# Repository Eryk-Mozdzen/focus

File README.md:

# FOCUS - BLDC motor control library

## Features

- FOC current loop implementation
- AB, AB+index, absolute encoder support
- [Sliding Mode Observer](https://www.mathworks.com/help/mcb/ref/slidingmodeobserver.html) method support
- [High Frequency Injection](https://www.sciencedirect.com/science/article/pii/S2214914723002155?fr=RR-2&ref=pdf_download&rr=a5664e15cb732783) method support
- automatic motor tunning
- C source code without external dependencies (even for `libm`)

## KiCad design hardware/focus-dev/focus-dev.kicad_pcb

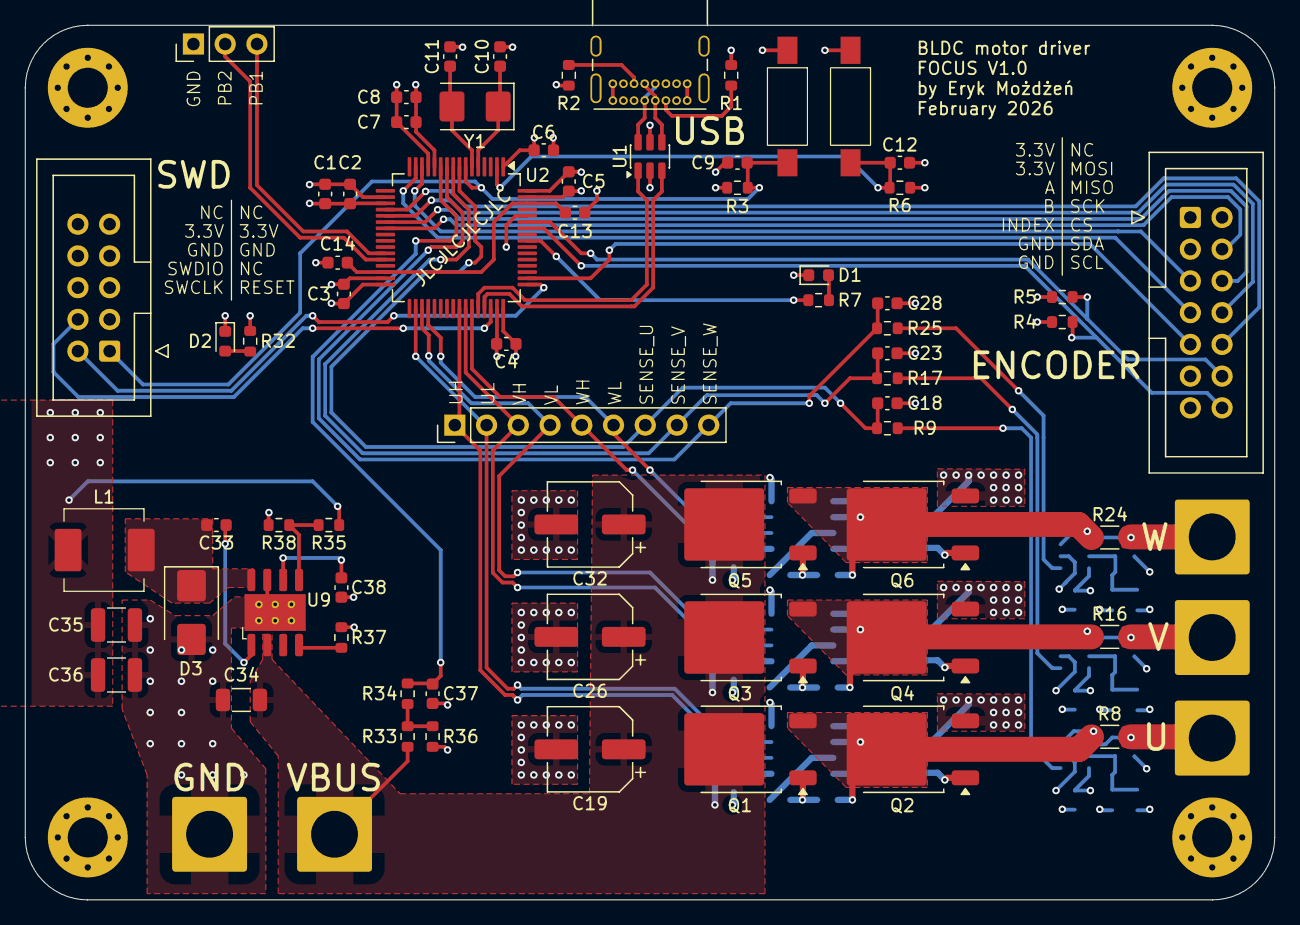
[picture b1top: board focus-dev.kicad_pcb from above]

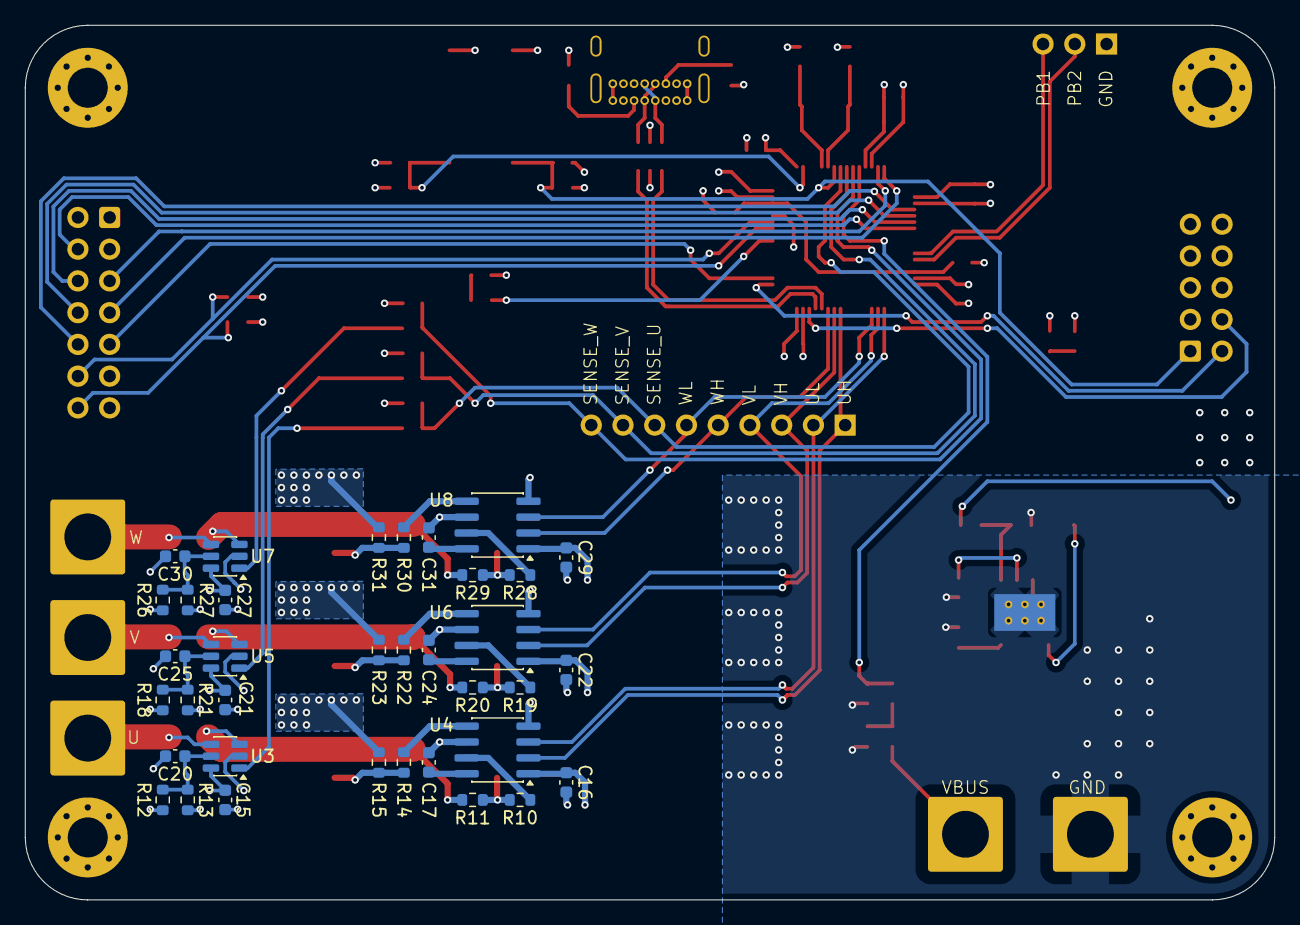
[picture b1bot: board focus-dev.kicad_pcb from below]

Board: 4 copper layers, 100.0 x 70.0 mm, 112 parts (36 on the bottom side), 73 nets.

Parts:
C1: 4.7u; C_0603_1608Metric
C2, C3, C4, C5, C6, C7, C9, C12, C15, C18, C20, C21, C23, C25, C27, C28, C30, C37: 100n; C_0603_1608Metric
C8: 1u; C_0603_1608Metric
C10, C11: 22p; C_0603_1608Metric
C13, C14: 2.2u; C_0603_1608Metric
C16, C22, C29: 1u/50V; C_0603_1608Metric
C17, C24, C31, C33: 100n/50V; C_0603_1608Metric
C19, C26, C32: 47u/50V; CP_Elec_6.3x7.7
C34: 10u/50V; C_1206_3216Metric
C35, C36: 47u/16V; C_1210_3225Metric
C38: 22n; C_0603_1608Metric
D1: BLUE; D_0603_1608Metric
D2: RED; D_0603_1608Metric
D3: SK56; D_SMB
H1, H2, H3, H4: MountingHole_Pad; MountingHole_3.2mm_M3_Pad_Via
J1: IDC-10; IDC-Header_2x05_P2.54mm_Vertical
J2: USB_C_Receptacle_USB2.0_14P; USB_C_Receptacle_GCT_USB4085
J3: IDC-14; IDC-Header_2x07_P2.54mm_Vertical
J4: Conn_01x09; PinHeader_1x09_P2.54mm_Vertical
J5: Conn_01x03; PinHeader_1x03_P2.54mm_Vertical
J6, J7, J8, J9, J10: Conn_01x01; SolderWire-4sqmm_1x01_D3mm_OD6mm
L1: 6.8u/4.5A; PA4341.XXXNLT
Q1, Q2, Q3, Q4, Q5, Q6: IPD90N04S4L04; TO-252-2
R1, R2: 5.1k; R_0603_1608Metric
R3, R4, R5, R12, R13, R18, R21, R26, R27: 4.7k; R_0603_1608Metric
R6: 10k; R_0603_1608Metric
R7, R32: 1k; R_0603_1608Metric
R8, R16, R24: 2m; R_1206_3216Metric
R9, R17, R25, R34: 10; R_0603_1608Metric
R10, R14, R19, R22, R28, R30: 68; R_0603_1608Metric
R11, R15, R20, R23, R29, R31, R36: 47k; R_0603_1608Metric
R33: 470k; R_0603_1608Metric
R35: 100k/1%; R_0603_1608Metric
R37: 49.9k; R_0603_1608Metric
R38: 29.4k/1%; R_0603_1608Metric
SW1, SW2: SW_Push; spst_6x3mm
U1: USBLC6-2SC6; SOT-23-6
U2: STM32H523RET6; LQFP-64_10x10mm_P0.5mm
U3, U5, U7: INA181A3; SOT-23-6
U4, U6, U8: LM2105D; SOIC-8_3.9x4.9mm_P1.27mm
U9: LV14340
Y1: 8MHz; Crystal_SMD_5032-2Pin_5.0x3.2mm

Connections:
+3.3V: C1.1, C2.1, C3.1, C4.1, C5.1, C6.1, C7.1, C8.1, C15.1, C21.1, C27.1, C35.1, C36.1, J1.7, J1.8, J3.1, J3.3, L1.2, R3.1, R4.1, R5.1, R6.1, R12.2, R18.2, R26.2, R32.1, R35.1, U1.5 (VBUS), U2.1 (VBAT), U2.13 (VDDA), U2.19 (VDD), U2.32 (VDD), U2.48 (VDD), U2.64 (VDD), U3.6 (V+), U5.6 (V+), U7.6 (V+)
/control/ENCODER_A: J3.5, U2.14 (PA0)
/control/ENCODER_B: J3.7, U2.15 (PA1)
/control/ENCODER_I2C_SCL: J3.14, R4.2, U2.58 (PB6)
/control/ENCODER_I2C_SDA: J3.12, R5.2, U2.59 (PB7)
/control/ENCODER_INDEX: J3.9, U2.50 (PA15(JTDI))
/control/ENCODER_SPI_CS: J3.10, U2.20 (PA4)
/control/ENCODER_SPI_MISO: J3.6, U2.22 (PA6)
/control/ENCODER_SPI_MOSI: J3.4, U2.23 (PA7)
/control/ENCODER_SPI_SCK: J3.8, U2.21 (PA5)
/control/STM_OSC_IN: C10.1, U2.5 (PH0), Y1.1
/control/STM_OSC_OUT: C11.1, U2.6 (PH1), Y1.2
/control/STM_RESET: C9.1, J1.1, R3.2, SW1.2, U2.7 (NRST)
/control/STM_SWCLK: J1.2, U2.49 (PA14(JTCK)
/control/STM_SWDIO: J1.4, U2.46 (PA13(JTMS)
/control/STM_USB_D+: U1.3 (I/O2), U2.45 (PA12)
/control/STM_USB_D-: U1.1 (I/O1), U2.44 (PA11)
/control/STM_USER_BUTTON: C12.1, R6.2, SW2.2, U2.2 (PC13)
/control/STM_USER_GPIO1: J5.3, U2.27 (PB1)
/control/STM_USER_GPIO2: J5.2, U2.28 (PB2)
/control/STM_USER_LED: R7.1, U2.56 (PB4(NJTRST))
/control/STM_VCAP: C13.1, C14.1, U2.30 (VCAP), U2.62 (VCAP)
/control/USB_CC1: J2.A5 (CC1), R1.2
/control/USB_CC2: J2.B5 (CC2), R2.2
/control/USB_D+: J2.A6 (D+), J2.B6 (D+), U1.4 (I/O2)
/control/USB_D-: J2.A7 (D-), J2.B7 (D-), U1.6 (I/O1)
/inverter/PHASE_U: C17.2, Q1.3 (S), Q2.2 (D), R8.1, R11.2, U3.3 (+), U4.6 (SH)
/inverter/PHASE_V: C24.2, Q3.3 (S), Q4.2 (D), R16.1, R20.2, U5.3 (+), U6.6 (SH)
/inverter/PHASE_W: C31.2, Q5.3 (S), Q6.2 (D), R24.1, R29.2, U7.3 (+), U8.6 (SH)
GND: C1.2, C2.2, C3.2, C4.2, C5.2, C6.2, C7.2, C8.2, C9.2, C10.2, C11.2, C12.2, C13.2, C14.2, C15.2, C16.1, C18.2, C19.2, C20.2, C21.2, C22.1, C23.2, C25.2, C26.2, C27.2, C28.2, C29.1, C30.2, C32.2, C34.2, C35.2, C36.2, C37.2, C38.1, D1.1 (K), D2.1 (K), D3.2 (A), J1.5, J1.6, J2.A1 (GND), J2.A12 (GND), J2.B1 (GND), J2.B12 (GND), J3.11, J3.13, J5.1, J10.1, Q2.3 (S), Q4.3 (S), Q6.3 (S), R1.1, R2.1, R13.2, R15.2, R21.2, R23.2, R27.2, R31.2, R36.2, R37.2, R38.2, SW1.1, SW2.1, U1.2 (GND), U2.12 (VSSA), U2.18 (VSS), U2.31 (VSS), U2.47 (VSS), U2.60 (BOOT0), U2.63 (VSS), U3.2 (GND), U4.4 (GND), U5.2 (GND), U6.4 (GND), U7.2 (GND), U8.4 (GND), U9.7 (GND), U9.9 (PAD)
MOTOR_PWM_UH: J4.1, U2.41 (PA8), U4.2 (INH)
MOTOR_PWM_UL: J4.2, U2.34 (PB13), U4.3 (INL)
MOTOR_PWM_VH: J4.3, U2.42 (PA9), U6.2 (INH)
MOTOR_PWM_VL: J4.4, U2.35 (PB14), U6.3 (INL)
MOTOR_PWM_WH: J4.5, U2.43 (PA10), U8.2 (INH)
MOTOR_PWM_WL: J4.6, U2.36 (PB15), U8.3 (INL)
MOTOR_SENSE_U: C18.1, J4.7, R9.2, U2.8 (PC0)
MOTOR_SENSE_V: C23.1, J4.8, R17.2, U2.9 (PC1)
MOTOR_SENSE_W: C28.1, J4.9, R25.2, U2.10 (PC2)
unnamed: D1.2 (A), R7.2
unnamed: D2.2 (A), R32.2
unnamed: C33.2, D3.1 (K), L1.1, U9.8 (SW)
unnamed: J6.1, R8.2, U3.4 (-)
unnamed: J7.1, R16.2, U5.4 (-)
unnamed: J8.1, R24.2, U7.4 (-)
unnamed: Q1.1 (G), R10.2, R11.1
unnamed: Q2.1 (G), R14.2, R15.1
unnamed: Q3.1 (G), R19.2, R20.1
unnamed: Q4.1 (G), R22.2, R23.1
unnamed: Q5.1 (G), R28.2, R29.1
unnamed: Q6.1 (G), R30.2, R31.1
unnamed: R9.1, U3.1
unnamed: R17.1, U5.1
unnamed: R25.1, U7.1
unnamed: R33.2, R34.1, R36.1
unnamed: C20.1, R12.1, R13.1, U3.5 (REF)
unnamed: C17.1, U4.8 (BST)
unnamed: R10.1, U4.7 (GH)
unnamed: R14.1, U4.5 (GL)
unnamed: C25.1, R18.1, R21.1, U5.5 (REF)
unnamed: C24.1, U6.8 (BST)
unnamed: R19.1, U6.7 (GH)
unnamed: R22.1, U6.5 (GL)
unnamed: C30.1, R26.1, R27.1, U7.5 (REF)
unnamed: C31.1, U8.8 (BST)
unnamed: R28.1, U8.7 (GH)
unnamed: R30.1, U8.5 (GL)
unnamed: C33.1, U9.1 (BOOT)
unnamed: R35.2, R38.1, U9.5 (FB)
unnamed: R37.1, U9.4 (RT/SYNC)
unnamed: C38.2, U9.6 (SS)
POWER_SENSE: C37.1, R34.2, U2.11 (PC3)
VBUS: C16.2, C19.1, C22.2, C26.1, C29.2, C32.1, C34.1, J9.1, Q1.2 (D), Q3.2 (D), Q5.2 (D), R33.1, U4.1 (GVDD), U6.1 (GVDD), U8.1 (GVDD), U9.2 (VIN)

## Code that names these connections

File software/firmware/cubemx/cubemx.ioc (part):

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Mcu.Name=STM32H523RETx
Mcu.Package=LQFP64
Mcu.UserName=STM32H523RETx
PA0.Signal=S_TIM2_CH1
PA1.Signal=S_TIM2_CH2
PA10.Signal=S_TIM1_CH3
PA11.Mode=Device
PA11.Signal=USB_DM
PA12.Mode=Device
PA12.Signal=USB_DP
PA15(JTDI).Signal=S_TIM2_ETR
PA8.Signal=S_TIM1_CH1
PA9.Signal=S_TIM1_CH2
PB1.Signal=GPIO_Output
PB13.Mode=PWM Generation1 CH1 CH1N
PB13.Signal=TIM1_CH1N
PB14.Mode=PWM Generation2 CH2 CH2N
PB14.Signal=TIM1_CH2N
PB15.Mode=PWM Generation3 CH3 CH3N
PB15.Signal=TIM1_CH3N
PB2.Signal=GPIO_Output
PB4(NJTRST).Signal=GPIO_Output
PC0.Signal=ADCx_INP10
PC1.Signal=ADCx_INP11
PC13.Signal=GPIO_Input
PC2.Signal=ADCx_INP12
PC3.Signal=ADCx_INP13
PH0-OSC_IN(PH0).Mode=HSE-External-Oscillator
PH0-OSC_IN(PH0).Signal=RCC_OSC_IN
PH1-OSC_OUT(PH1).Mode=HSE-External-Oscillator
PH1-OSC_OUT(PH1).Signal=RCC_OSC_OUT
RCC.HSE_VALUE=8000000
RCC.SYSCLKFreq_VALUE=250000000
RCC.SYSCLKSource=RCC_SYSCLKSOURCE_PLLCLK
board=custom

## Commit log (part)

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2025-07-21 driver architecture
2025-07-22 basic foc
2025-07-22 memory
2025-07-24 move code to external directory
2026-01-01 trash
2026-01-04 wip: dev-board schematic
2026-01-28 wip: remove onboard encoders
2026-01-31 wip: layout
2026-02-01 wip: rest of the layout
2026-02-01 wip: change resistor value
2026-02-21 blink project
2026-02-21 TinyUSB CDC & MSC
2026-02-22 lwip, USB-Ethernet HTTP server
2026-02-22 remove FreeRTOS, add UDP stream
2026-02-23 wip: cleaning
2026-02-24 focus source code architecture
2026-02-26 MQTT pub/sub
2026-02-27 MSGPACK
2026-02-27 cleaning
2026-02-28 cleaning, PWM wip
2026-02-28 fix encoder index interrupt
2026-03-01 first motor spin
2026-03-02 first FOC
2026-03-04 wip: encoder misaligment calibration, proper SVPWM
2026-03-05 PWM 10kHz, preload disabled
2026-03-06 encoder eccentricity calibration, current offset calibration
2026-03-07 cleaner encoder calibration (still not work)
2026-03-08 poorly tuned FOC
2026-04-30 allow for uv
2026-04-30 telnet support
2026-05-03 FSM, move math to separate file
2026-05-03 automatic Rs Ld Lq estimation
2026-05-03 cleaning configs
2026-05-06 simplify PID antiwindup logic
2026-05-07 fix dt pid
2026-05-07 calibration of current offset and scale
2026-05-08 wip: FOC works, example PD for position control
2026-05-09 reorganize repo files
2026-05-09 fix build system
2026-05-10 remove open loop
2026-05-10 remove position measurement from motor calibration for Rs, Ld, Lq
2026-05-10 fix encoder macros
2026-05-10 pack claibration context into one union
2026-05-10 #define to disable encoder support, Sliding Mode Observer implementation
2026-05-10 fix antiwindup for PI
2026-05-11 constants for LPF, remove unused scripts
2026-05-13 High Frequency Injection (still not work)
2026-05-16 HFI SDFT also not work yet
2026-05-17 better scope.py app
2026-05-18 better scope.py
2026-05-21 HFI works kinda
2026-06-05 idk why HFI not work
2026-06-05 remove HFI, adding open loop ramp instead WIP
2026-06-05 move SMO to separate file, run SMO during startup ramp as well
2026-06-05 add biquad filter to angular velocity in SMO
2026-06-06 automatic return to ALIGN & RAMP state when velocity is to low
2026-06-06 remove get_position() for sensorless application
2026-06-06 convert torque setpoint to Iq current setpoint
2026-06-06 better name
2026-06-07 major state machine and configuration refactor
2026-06-07 fixes of the AB & ABI operation
2026-06-07 allow hardware without native INDEX functionality
2026-06-20 save accentricity data when AB encder in RAM
2026-06-20 new API and async state callback
2026-06-21 better SMO g factor
2026-06-21 test absolute encoder, make eccentricity lookup table 16-bit
